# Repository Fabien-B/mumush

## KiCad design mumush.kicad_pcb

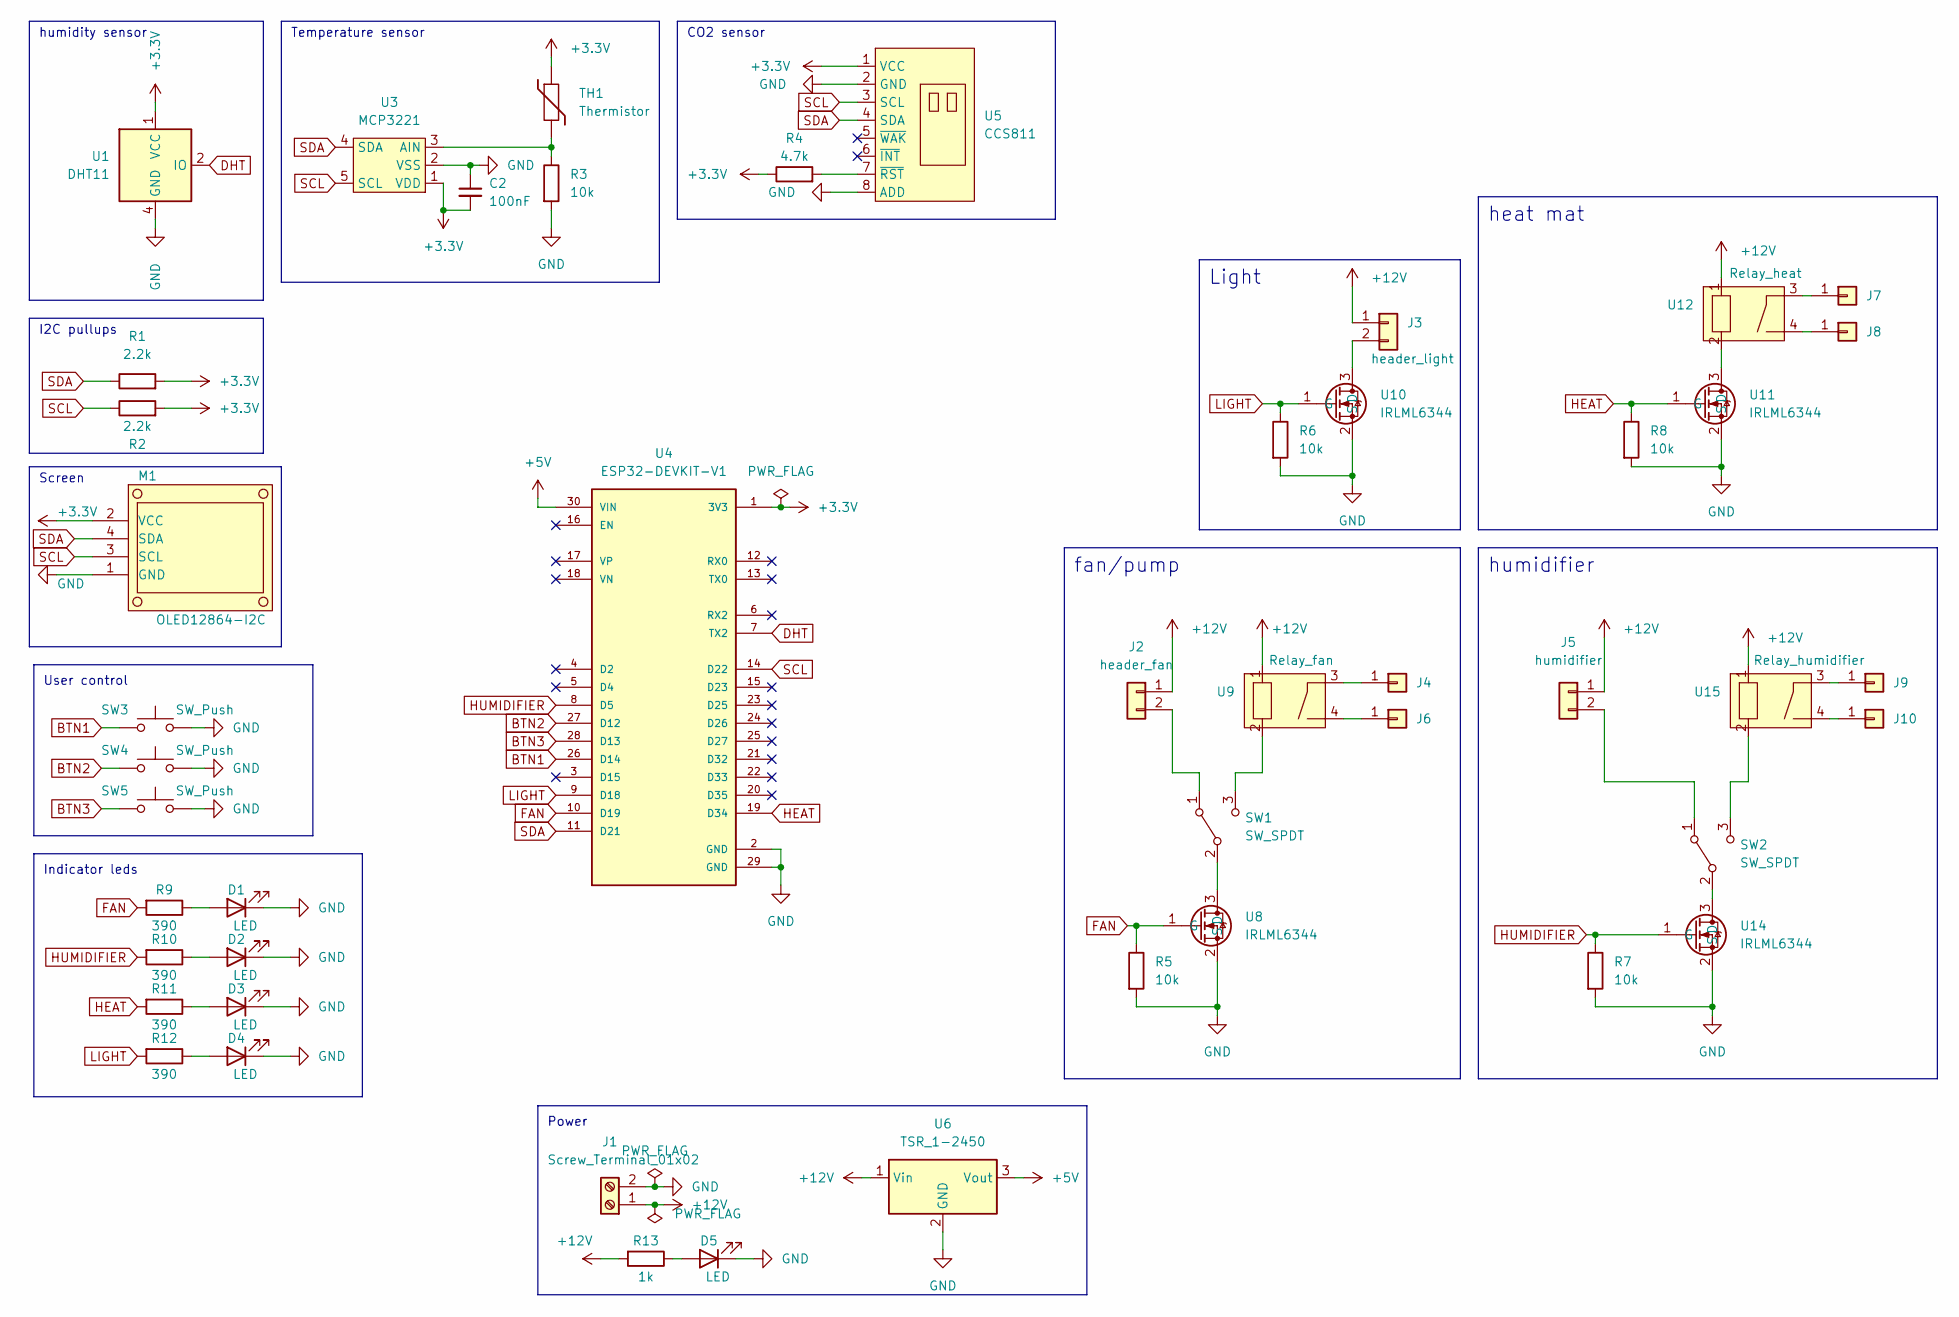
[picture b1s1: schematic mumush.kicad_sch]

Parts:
C2: 100nF; C_0603_1608Metric_Pad1.08x0.95mm_HandSolder
D1, D2, D3, D4, D5: LED; LED_0603_1608Metric_Pad1.05x0.95mm_HandSolder
J1: Screw_Terminal_01x02; TerminalBlock_bornier-2_P5.08mm
J2: header_fan; PinHeader_1x02_P2.54mm_Horizontal
J3: header_light; PinHeader_1x02_P2.54mm_Horizontal
J4, J6, J7, J8, J9, J10: Conn_01x01; cosse
J5: humidifier; PinHeader_1x02_P2.54mm_Horizontal
M1: OLED12864-I2C; OLED12864-I2C_TH_6mm
R1, R2: 2.2k; R_0603_1608Metric_Pad0.98x0.95mm_HandSolder
R3, R5, R6, R7, R8: 10k; R_0603_1608Metric_Pad0.98x0.95mm_HandSolder
R4: 4.7k; R_0603_1608Metric_Pad0.98x0.95mm_HandSolder
R9, R10, R11, R12: 390; R_0603_1608Metric_Pad0.98x0.95mm_HandSolder
R13: 1k; R_0603_1608Metric_Pad0.98x0.95mm_HandSolder
SW1, SW2: SW_SPDT; switch SPDT
SW3, SW4, SW5: SW_Push; SW_PUSH_6mm_H5mm
TH1: Thermistor; PinHeader_1x02_P2.54mm_Vertical
U1: DHT11; PinHeader_1x04_P2.54mm_Vertical
U3: MCP3221; SOT-23-5
U4: ESP32-DEVKIT-V1; MODULE_ESP32_DEVKIT_V1; PARTREV N/A
U5: CCS811; PinHeader_1x08_P2.54mm_Vertical
U6: TSR_1-2450; Converter_DCDC_TRACO_TSR-1_THT
U8, U10, U11, U14: IRLML6344; SOT-23
U9: Relay_fan; relay OJE 112HMFF000
U12: Relay_heat; relay OJE 112HMFF000
U15: Relay_humidifier; relay OJE 112HMFF000

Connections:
+3.3V: C2.2, M1.2 (VCC), R1.2, R2.2, R4.1, TH1.1, U1.1 (VCC), U3.1 (VDD), U4.1 (3V3), U5.1 (VCC)
+5V: U4.30 (VIN), U6.3 (Vout)
+12V: J1.1, J2.1, J3.1, J5.1, R13.2, U6.1 (Vin), U9.1, U12.1, U15.1
BTN1: SW3.1, U4.26 (D14)
BTN2: SW4.1, U4.27 (D12)
BTN3: SW5.1, U4.28 (D13)
DHT: U1.2 (IO), U4.7 (TX2)
FAN: R5.1, R9.2, U4.10 (D19), U8.1 (G)
GND: C2.1, D1.1 (K), D2.1 (K), D3.1 (K), D4.1 (K), D5.1 (K), J1.2, M1.1 (GND), R3.2, R5.2, R6.2, R7.2, R8.2, SW3.2, SW4.2, SW5.2, U1.4 (GND), U3.2 (VSS), U4.2 (GND), U4.29 (GND), U5.2 (GND), U5.8 (ADD), U6.2 (GND), U8.2 (S), U10.2 (S), U11.2 (S), U14.2 (S)
HEAT: R8.1, R11.2, U4.19 (D34), U11.1 (G)
HUMIDIFIER: R7.1, R10.2, U4.8 (D5), U14.1 (G)
LIGHT: R6.1, R12.2, U4.9 (D18), U10.1 (G)
unnamed: D1.2 (A), R9.1
unnamed: D2.2 (A), R10.1
unnamed: D3.2 (A), R11.1
unnamed: D4.2 (A), R12.1
unnamed: D5.2 (A), R13.1
unnamed: J2.2, SW1.1 (A)
unnamed: J3.2, U10.3 (D)
unnamed: J4.1, U9.3
unnamed: J6.1, U9.4
unnamed: J7.1, U12.3
unnamed: J8.1, U12.4
unnamed: J9.1, U15.3
unnamed: J10.1, U15.4
unnamed: R3.1, TH1.2, U3.3 (AIN)
unnamed: R4.2, U5.7 (~RST)
unnamed: SW1.2 (B), U8.3 (D)
unnamed: SW1.3 (C), U9.2
unnamed: J5.2, SW2.1 (A)
unnamed: SW2.2 (B), U14.3 (D)
unnamed: SW2.3 (C), U15.2
unnamed: U11.3 (D), U12.2
SCL: M1.3 (SCL), R2.1, U3.5 (SCL), U4.14 (D22), U5.3 (SCL)
SDA: M1.4 (SDA), R1.1, U3.4 (SDA), U4.11 (D21), U5.4 (SDA)

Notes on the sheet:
Temperature sensor
heat mat
Light
CO2 sensor
humidity sensor
I2C pullups
Power
User control
humidifier
Screen
fan/pump
Indicator leds

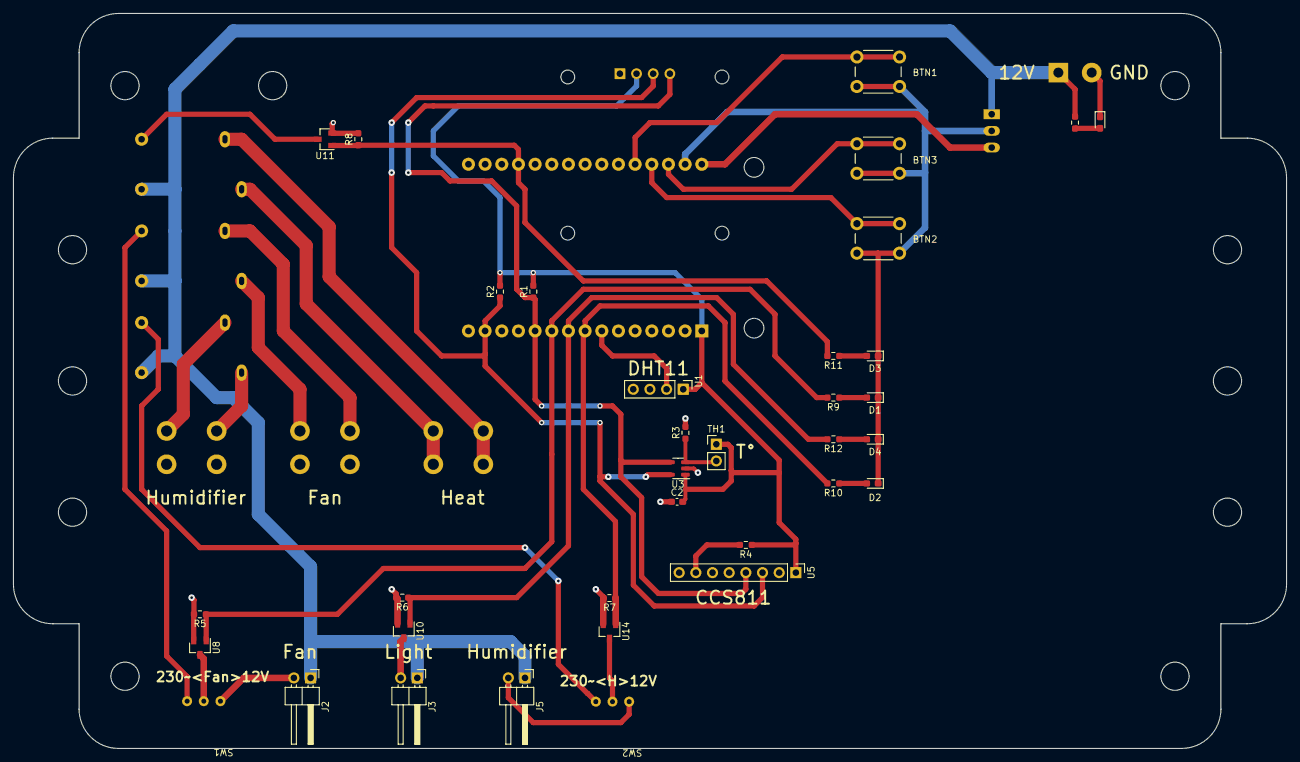
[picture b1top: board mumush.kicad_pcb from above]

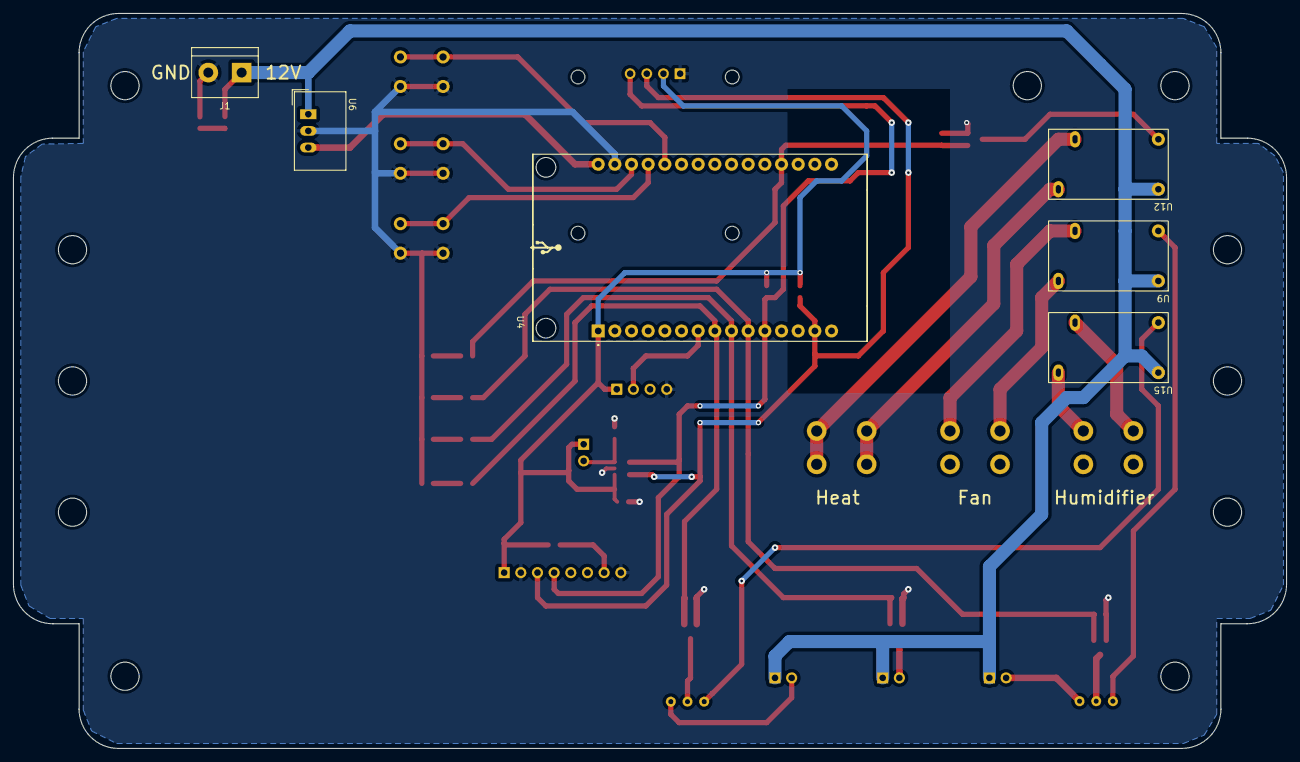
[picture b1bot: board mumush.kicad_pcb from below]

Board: 2 copper layers, 194.0 x 112.0 mm, 48 parts (12 on the bottom side), 35 nets.

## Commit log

2023-01-05 update libs
2023-01-05 clean
2023-01-06 disable ACDC converter.
2023-01-10 progress on schematic.
2023-01-10 choose better footprints.
2023-01-11 update OLED screen.
2023-02-03 PCB progress.
2023-02-03 update libs.
